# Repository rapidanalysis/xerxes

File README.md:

# Xerxes Pi — CM4/CM5 Carrier Board - Rev 2

## Overview
The **Xerxes Pi** is a compact, high-performance carrier board designed for the **Raspberry Pi Compute Module 4 (CM4)** and **Compute Module 5 (CM5)**. It integrates essential interfaces, intelligent power delivery, and expansion options suitable for both prototyping and embedded product deployment.

## Features

- **Dual Hirose 100-pin connectors** (0.5 mm pitch) compatible with CM4 and CM5  
- **USB-C port** for both **data and power**  
- **Gigabit Ethernet** interface with ESD protection
- **MicroSD card slot** for CM4 and CM5 Lite models  
- **M.2 M-Key connector** with onboard regulated power supply  
- **Boot-mode jumper** for eMMC variants of compute modules  
- **UART debug header** for serial console access  
- **I²C Qwiic connector** for peripheral expansion  
- **Fan header** for active cooling control  
- **External power input** connector  
- **Integrated PoE+ module** (IEEE 802.3at compliant)  
- **Indicator LEDs** for power and status monitoring

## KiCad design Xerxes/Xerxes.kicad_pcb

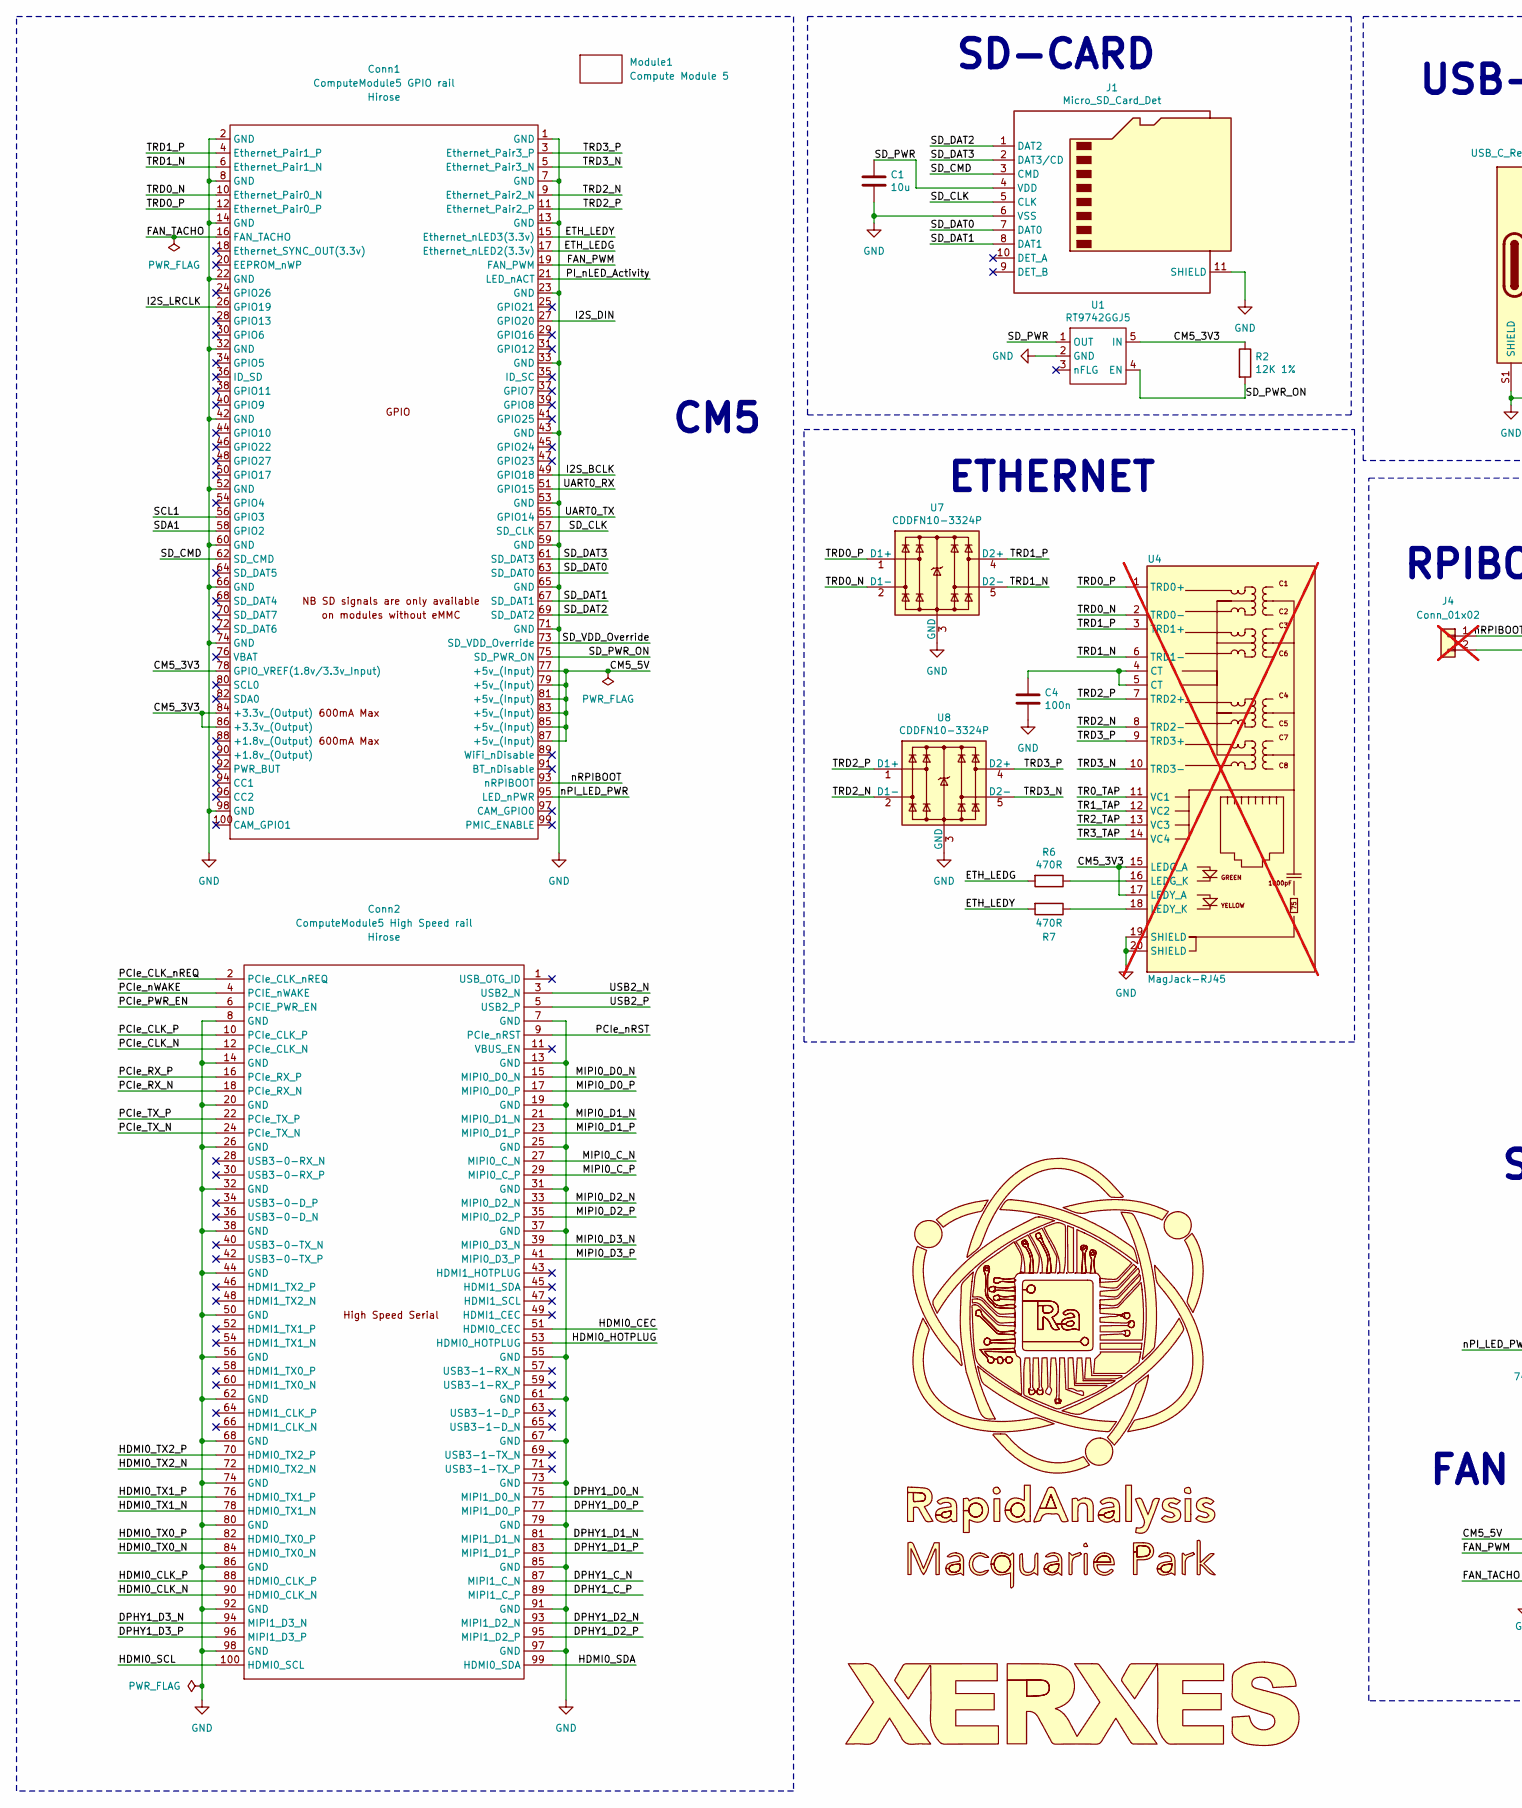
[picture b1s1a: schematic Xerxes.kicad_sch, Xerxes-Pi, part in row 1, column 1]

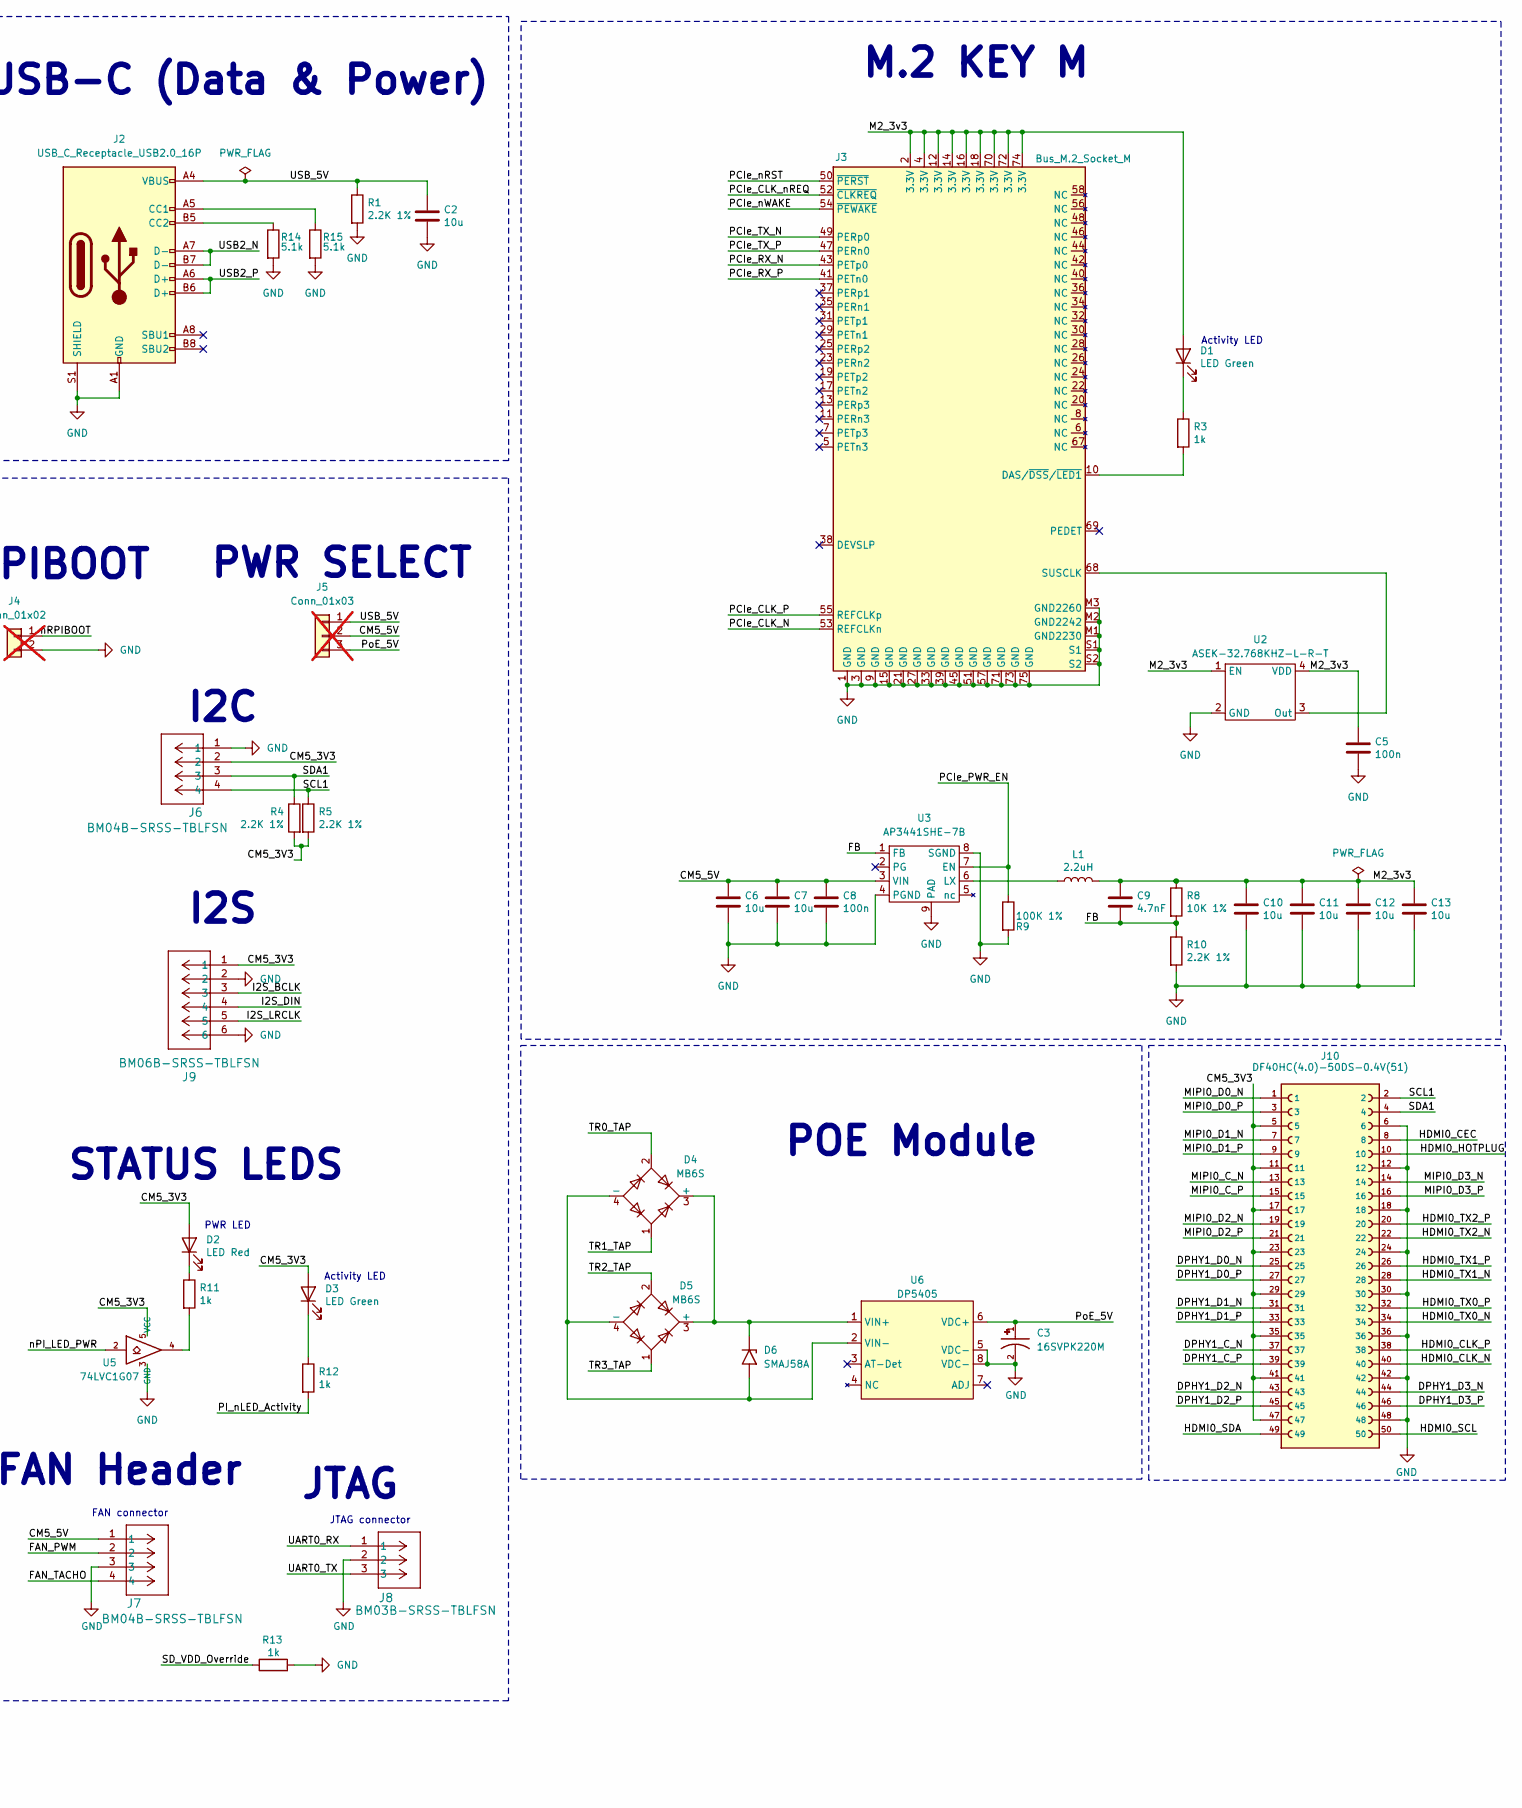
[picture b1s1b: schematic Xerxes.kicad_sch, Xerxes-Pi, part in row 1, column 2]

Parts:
C1, C2, C6, C7, C10, C11, C12, C13: 10u; C_0805_2012Metric; MPN GRM21BR71A106KA73L
C3: 16SVPK220M; CAP_16SVPK220M; MPN 16SVPK220M
C4, C5, C8: 100n; C_0402_1005Metric; MPN EMK105B7104KV-F
C9: 4.7nF; C_0402_1005Metric; MPN CC0402KRX7R9BB472
Conn1: ComputeModule5 GPIO rail; CONN_DF40C-100DS-0.4V51_HIR; MPN DF40C-100DS-0.4V(51)
Conn2: ComputeModule5 High Speed rail; CONN_DF40C-100DS-0.4V51_HIR; MPN DF40C-100DS-0.4V(51)
D1, D3: LED Green; LED_0603_1608Metric; MPN LTST-C190GKT
D2: LED Red; LED_0603_1608Metric; MPN LTST-C190KRKT
D4, D5: MB6S; TO-269AA; MPN MB6S
D6: SMAJ58A; D_SMA; MPN SMAJ58A
J1: Micro_SD_Card_Det; SDCARD_MOLEX_503398-1892; MPN 5033981892
J2: USB_C_Receptacle_USB2.0_16P; USB4205-GF-A; MPN USB4205-GF-A
J3: Bus_M.2_Socket_M; M.2 M Key socket; MPN MDT320M03001
J4: Conn_01x02; PinHeader_1x02_P2.54mm_Vertical; MPN G800W306018EU; not fitted
J5: Conn_01x03; PinHeader_1x03_P2.54mm_Vertical; MPN G800W305018EU; not fitted
J6, J7: BM04B-SRSS-TBLFSN; JST_SH_BM04B-SRSS-TB_1x04-1MP_P1.00mm_Vertical; MPN BM04B-SRSS-TBLFSN
J8: BM03B-SRSS-TBLFSN; JST_SH_BM03B-SRSS-TB_1x03-1MP_P1.00mm_Vertical; MPN BM03B-SRSS-TBLFSN
J9: BM06B-SRSS-TBLFSN; CONN_BM06B-SRSS-TB_JST; MPN BM06B-SRSS-TBLFSN
J10: DF40HC(4.0)-50DS-0.4V(51); HRS_DF40HC_4.0_-50DS-0.4V_51_; MPN DF40HC(4.0)-50DS-0.4V(51)
L1: 2.2uH; L_Bourns_SRP5030CC; MPN SRP5030CC-2R2M
Module1: Compute Module 5; Raspberry-Pi-5-Compute-Module
R1, R4, R5, R10: 2.2K 1%; R_0402_1005Metric; MPN RC0402FR-072K2L
R2: 12K 1%; R_0402_1005Metric; MPN RC0402FR-0712KL
R3, R11, R12, R13: 1k; R_0402_1005Metric; MPN RC0402FR-071KL
R6, R7: 470R; R_0402_1005Metric; MPN RC0402FR-07470RL
R8: 10K 1%; R_0402_1005Metric; MPN RC0402FR-0710KL
R9: 100K 1%; R_0402_1005Metric; MPN RC0402FR-07100KL
R14, R15: 5.1k; R_0603_1608Metric; MPN RC0603FR-075K1L
Sym1: Xerxes_Logo
Sym2: RapidAnalysis_Logo
U1: RT9742GGJ5; SOT-23-5; MPN RT9742GGJ5
U2: ASEK-32.768KHZ-L-R-T; Crystal_SMD_3225-4Pin_3.2x2.5mm; MPN ASEK-32.768KHZ-L-R-T
U3: AP3441SHE-7B; DFN-8-1EP_2x2mm_P0.5mm_EP1.05x1.75mm; MPN AP3441SHE-7B
U4: MagJack-RJ45; TRJG0926HENL; MPN LPJG0926HENL; not fitted
U5: 74LVC1G07; SOT-353_SC-70-5; MPN 74LVC1G07
U6: DP5405
U7, U8: CDDFN10-3324P; USON-10_2.5x1.0mm_P0.5mm; MPN CDDFN10-3324P

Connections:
/CM5_3V3: Conn1.78 (GPIO_VREF(1.8v/3.3v_Input)), Conn1.84 (+3.3v_(Output)), Conn1.86 (+3.3v_(Output)), D2.2 (A), D3.2 (A), J6.2, J9.1, J10.5, J10.11, J10.17, J10.23, J10.29, J10.35, J10.41, J10.47, R2.1, R4.2, R5.2, U1.5 (IN), U4.15 (LEDG_A), U4.17 (LEDY_A), U5.5 (VCC)
/CM5_5V: C6.1, C7.1, C8.1, Conn1.77 (+5v_(Input)), Conn1.79 (+5v_(Input)), Conn1.81 (+5v_(Input)), Conn1.83 (+5v_(Input)), Conn1.85 (+5v_(Input)), Conn1.87 (+5v_(Input)), J5.2, J7.1, U3.3 (VIN)
/DPHY1_C_N: Conn2.87 (MIPI1_C_N), J10.37
/DPHY1_C_P: Conn2.89 (MIPI1_C_P), J10.39
/DPHY1_D0_N: Conn2.75 (MIPI1_D0_N), J10.25
/DPHY1_D0_P: Conn2.77 (MIPI1_D0_P), J10.27
/DPHY1_D1_N: Conn2.81 (MIPI1_D1_N), J10.31
/DPHY1_D1_P: Conn2.83 (MIPI1_D1_P), J10.33
/DPHY1_D2_N: Conn2.93 (MIPI1_D2_N), J10.43
/DPHY1_D2_P: Conn2.95 (MIPI1_D2_P), J10.45
/DPHY1_D3_N: Conn2.94 (MIPI1_D3_N), J10.44
/DPHY1_D3_P: Conn2.96 (MIPI1_D3_P), J10.46
/ETH_LEDG: Conn1.17 (Ethernet_nLED2(3.3v)), R6.2
/ETH_LEDY: Conn1.15 (Ethernet_nLED3(3.3v)), R7.2
/FAN_PWM: Conn1.19 (FAN_PWM), J7.2
/FAN_TACHO: Conn1.16 (FAN_TACHO), J7.4
/FB: C9.2, R8.2, R10.1, U3.1 (FB)
/HDMI0_CEC: Conn2.51 (HDMI0_CEC), J10.8
/HDMI0_CLK_N: Conn2.90 (HDMI0_CLK_N), J10.40
/HDMI0_CLK_P: Conn2.88 (HDMI0_CLK_P), J10.38
/HDMI0_HOTPLUG: Conn2.53 (HDMI0_HOTPLUG), J10.10
/HDMI0_SCL: Conn2.100 (HDMI0_SCL), J10.50
/HDMI0_SDA: Conn2.99 (HDMI0_SDA), J10.49
/HDMI0_TX0_N: Conn2.84 (HDMI0_TX0_N), J10.34
/HDMI0_TX0_P: Conn2.82 (HDMI0_TX0_P), J10.32
/HDMI0_TX1_N: Conn2.78 (HDMI0_TX1_N), J10.28
/HDMI0_TX1_P: Conn2.76 (HDMI0_TX1_P), J10.26
/HDMI0_TX2_N: Conn2.72 (HDMI0_TX2_N), J10.22
/HDMI0_TX2_P: Conn2.70 (HDMI0_TX2_P), J10.20
/I2S_BCLK: Conn1.49 (GPIO18), J9.3
/I2S_DIN: Conn1.27 (GPIO20), J9.4
/I2S_LRCLK: Conn1.26 (GPIO19), J9.5
/M2_3v3: C5.1, C9.1, C10.1, C11.1, C12.1, C13.1, D1.2 (A), J3.2 (3.3V), J3.4 (3.3V), J3.12 (3.3V), J3.14 (3.3V), J3.16 (3.3V), J3.18 (3.3V), J3.70 (3.3V), J3.72 (3.3V), J3.74 (3.3V), L1.2, R8.1, U2.1 (EN), U2.4 (VDD)
/MIPI0_C_N: Conn2.27 (MIPI0_C_N), J10.13
/MIPI0_C_P: Conn2.29 (MIPI0_C_P), J10.15
/MIPI0_D0_N: Conn2.15 (MIPI0_D0_N), J10.1
/MIPI0_D0_P: Conn2.17 (MIPI0_D0_P), J10.3
/MIPI0_D1_N: Conn2.21 (MIPI0_D1_N), J10.7
/MIPI0_D1_P: Conn2.23 (MIPI0_D1_P), J10.9
/MIPI0_D2_N: Conn2.33 (MIPI0_D2_N), J10.19
/MIPI0_D2_P: Conn2.35 (MIPI0_D2_P), J10.21
/MIPI0_D3_N: Conn2.39 (MIPI0_D3_N), J10.14
/MIPI0_D3_P: Conn2.41 (MIPI0_D3_P), J10.16
/PCIe_CLK_N: Conn2.12 (PCIe_CLK_N), J3.53 (REFCLKn)
/PCIe_CLK_P: Conn2.10 (PCIe_CLK_P), J3.55 (REFCLKp)
/PCIe_CLK_nREQ: Conn2.2 (PCIe_CLK_nREQ), J3.52 (~CLKREQ)
/PCIe_PWR_EN: Conn2.6 (PCIE_PWR_EN), R9.1, U3.7 (EN)
/PCIe_RX_N: Conn2.18 (PCIe_RX_N), J3.43 (PETp0)
/PCIe_RX_P: Conn2.16 (PCIe_RX_P), J3.41 (PETn0)
/PCIe_TX_N: Conn2.24 (PCIe_TX_N), J3.49 (PERp0)
/PCIe_TX_P: Conn2.22 (PCIe_TX_P), J3.47 (PERn0)
/PCIe_nRST: Conn2.9 (PCIe_nRST), J3.50 (~PERST)
/PCIe_nWAKE: Conn2.4 (PCIE_nWAKE), J3.54 (~PEWAKE)
/PI_nLED_Activity: Conn1.21 (LED_nACT), R12.2
/PoE_5V: C3.1, J5.3, U6.6 (VDC+)
/SCL1: Conn1.56 (GPIO3), J6.4, J10.2, R5.1
/SDA1: Conn1.58 (GPIO2), J6.3, J10.4, R4.1
/SD_CLK: Conn1.57 (SD_CLK), J1.5 (CLK)
/SD_CMD: Conn1.62 (SD_CMD), J1.3 (CMD)
/SD_DAT0: Conn1.63 (SD_DAT0), J1.7 (DAT0)
/SD_DAT1: Conn1.67 (SD_DAT1), J1.8 (DAT1)
/SD_DAT2: Conn1.69 (SD_DAT2), J1.1 (DAT2)
/SD_DAT3: Conn1.61 (SD_DAT3), J1.2 (DAT3/CD)
/SD_PWR: C1.1, J1.4 (VDD), U1.1 (OUT)
/SD_PWR_ON: Conn1.75 (SD_PWR_ON), R2.2, U1.4 (EN)
/SD_VDD_Override: Conn1.73 (SD_VDD_Override), R13.1
/TR0_TAP: D4.2, U4.11 (VC1)
/TR1_TAP: D4.1, U4.12 (VC2)
/TR2_TAP: D5.2, U4.13 (VC3)
/TR3_TAP: D5.1, U4.14 (VC4)
/TRD0_N: Conn1.10 (Ethernet_Pair0_N), U4.2 (TRD0-), U7.2 (D1-), U7.9
/TRD0_P: Conn1.12 (Ethernet_Pair0_P), U4.1 (TRD0+), U7.1 (D1+), U7.10
/TRD1_N: Conn1.6 (Ethernet_Pair1_N), U4.6 (TRD1-), U7.5 (D2-), U7.6
/TRD1_P: Conn1.4 (Ethernet_Pair1_P), U4.3 (TRD1+), U7.4 (D2+), U7.7
/TRD2_N: Conn1.9 (Ethernet_Pair2_N), U4.8 (TRD2-), U8.2 (D1-), U8.9
/TRD2_P: Conn1.11 (Ethernet_Pair2_P), U4.7 (TRD2+), U8.1 (D1+), U8.10
/TRD3_N: Conn1.5 (Ethernet_Pair3_N), U4.10 (TRD3-), U8.5 (D2-), U8.6
/TRD3_P: Conn1.3 (Ethernet_Pair3_P), U4.9 (TRD3+), U8.4 (D2+), U8.7
/UART0_RX: Conn1.51 (GPIO15), J8.1
/UART0_TX: Conn1.55 (GPIO14), J8.3
/USB2_N: Conn2.3 (USB2_N), J2.A7 (D-), J2.B7 (D-)
/USB2_P: Conn2.5 (USB2_P), J2.A6 (D+), J2.B6 (D+)
/USB_5V: C2.1, J2.A4 (VBUS), J2.A9 (VBUS), J2.B4 (VBUS), J2.B9 (VBUS), J5.1, R1.1
/nPI_LED_PWR: Conn1.95 (LED_nPWR), U5.2
/nRPIBOOT: Conn1.93 (nRPIBOOT), J4.1
GND: C1.2, C2.2, C3.2, C4.2, C5.2, C6.2, C7.2, C8.2, C10.2, C11.2, C12.2, C13.2, Conn1.1 (GND), Conn1.2 (GND), Conn1.7 (GND), Conn1.8 (GND), Conn1.13 (GND), Conn1.14 (GND), Conn1.22 (GND), Conn1.23 (GND), Conn1.32 (GND), Conn1.33 (GND), Conn1.42 (GND), Conn1.43 (GND), Conn1.52 (GND), Conn1.53 (GND), Conn1.59 (GND), Conn1.60 (GND), Conn1.65 (GND), Conn1.66 (GND), Conn1.71 (GND), Conn1.74 (GND), Conn1.98 (GND), Conn2.7 (GND), Conn2.8 (GND), Conn2.13 (GND), Conn2.14 (GND), Conn2.19 (GND), Conn2.20 (GND), Conn2.25 (GND), Conn2.26 (GND), Conn2.31 (GND), Conn2.32 (GND), Conn2.37 (GND), Conn2.38 (GND), Conn2.44 (GND), Conn2.50 (GND), Conn2.55 (GND), Conn2.56 (GND), Conn2.61 (GND), Conn2.62 (GND), Conn2.67 (GND), Conn2.68 (GND), Conn2.73 (GND), Conn2.74 (GND), Conn2.79 (GND), Conn2.80 (GND), Conn2.85 (GND), Conn2.86 (GND), Conn2.91 (GND), Conn2.92 (GND), Conn2.97 (GND), Conn2.98 (GND), J1.6 (VSS), J1.11 (SHIELD), J2.A1 (GND), J2.A12 (GND), J2.B1 (GND), J2.B12 (GND), J2.S1 (SHIELD), J3.1 (GND), J3.3 (GND), J3.9 (GND), J3.15 (GND), J3.21 (GND), J3.27 (GND), J3.33 (GND), J3.39 (GND), J3.45 (GND), J3.51 (GND), J3.57 (GND), J3.71 (GND), J3.73 (GND), J3.75 (GND), J3.M1 (GND2230), J3.M2 (GND2242), J3.M3 (GND2260), J3.S1, J3.S2, J4.2, J6.1, J7.3, J8.2, J9.2, J9.6, J10.6, J10.12, J10.18, J10.24, J10.30, J10.36, J10.42, J10.48, R1.2, R9.2, R10.2, R13.2, R14.2, R15.2, U1.2 (GND), U2.2 (GND), U3.4 (PGND), U3.8 (SGND), U3.9 (PAD), U4.19 (SHIELD), U4.20 (SHIELD), U5.3 (GND), U6.5 (VDC-), U6.8 (VDC-), U7.3 (GND), U7.8 (GND), U8.3 (GND), U8.8 (GND)
unnamed: C4.1, U4.4 (CT), U4.5 (CT)
unnamed: D1.1 (K), R3.1
unnamed: D2.1 (K), R11.1
unnamed: D3.1 (K), R12.1
unnamed: D4.3 (+), D5.3 (+), D6.1 (A1), U6.1 (VIN+)
unnamed: D4.4 (-), D5.4 (-), D6.2 (A2), U6.2 (VIN-)
unnamed: J2.A5 (CC1), R15.1
unnamed: J2.B5 (CC2), R14.1
unnamed: J3.10 (DAS/~DSS/~LED1), R3.2
unnamed: J3.68 (SUSCLK), U2.3 (Out)
unnamed: R11.2, U5.4
unnamed: L1.1, U3.6 (LX)
unnamed: R6.1, U4.16 (LEDG_K)
unnamed: R7.1, U4.18 (LEDY_K)

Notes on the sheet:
USB-C (Data & Power)
JTAG connector
I2C
M.2 KEY M
POE Module
PWR SELECT
STATUS LEDS
Activity LED
PWR LED
I2S
FAN Header
FAN connector
RPIBOOT
JTAG
ETHERNET
CM5
SD-CARD

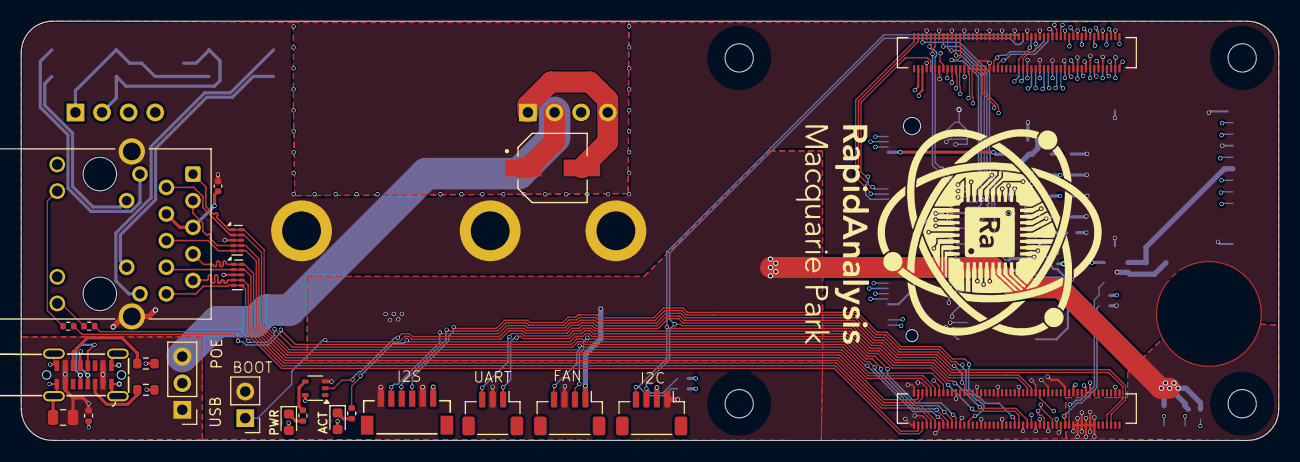
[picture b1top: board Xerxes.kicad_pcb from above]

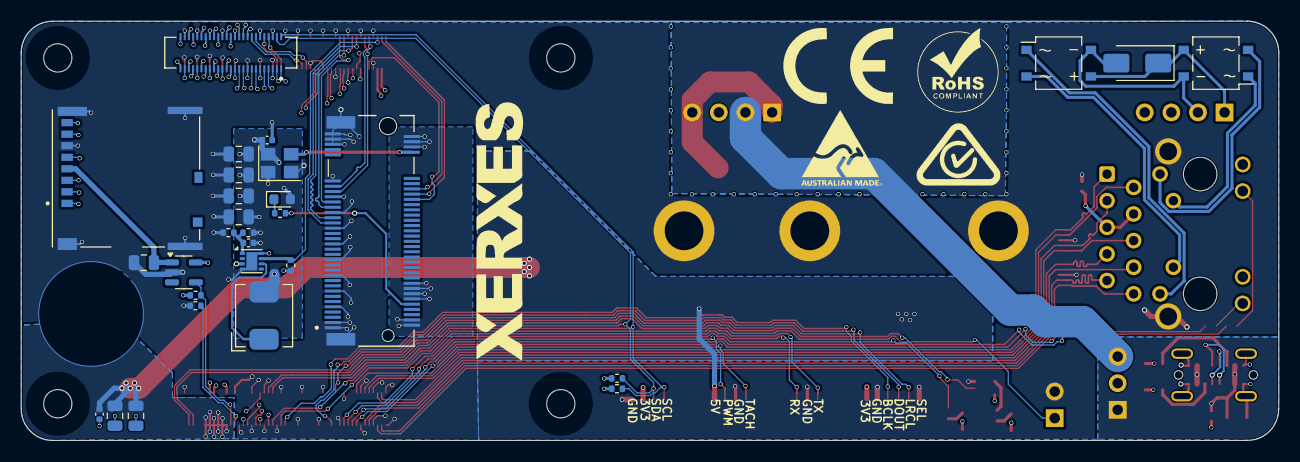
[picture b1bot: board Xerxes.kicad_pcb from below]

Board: 6 copper layers, 120.0 x 40.0 mm, 58 parts (30 on the bottom side), 100 nets.

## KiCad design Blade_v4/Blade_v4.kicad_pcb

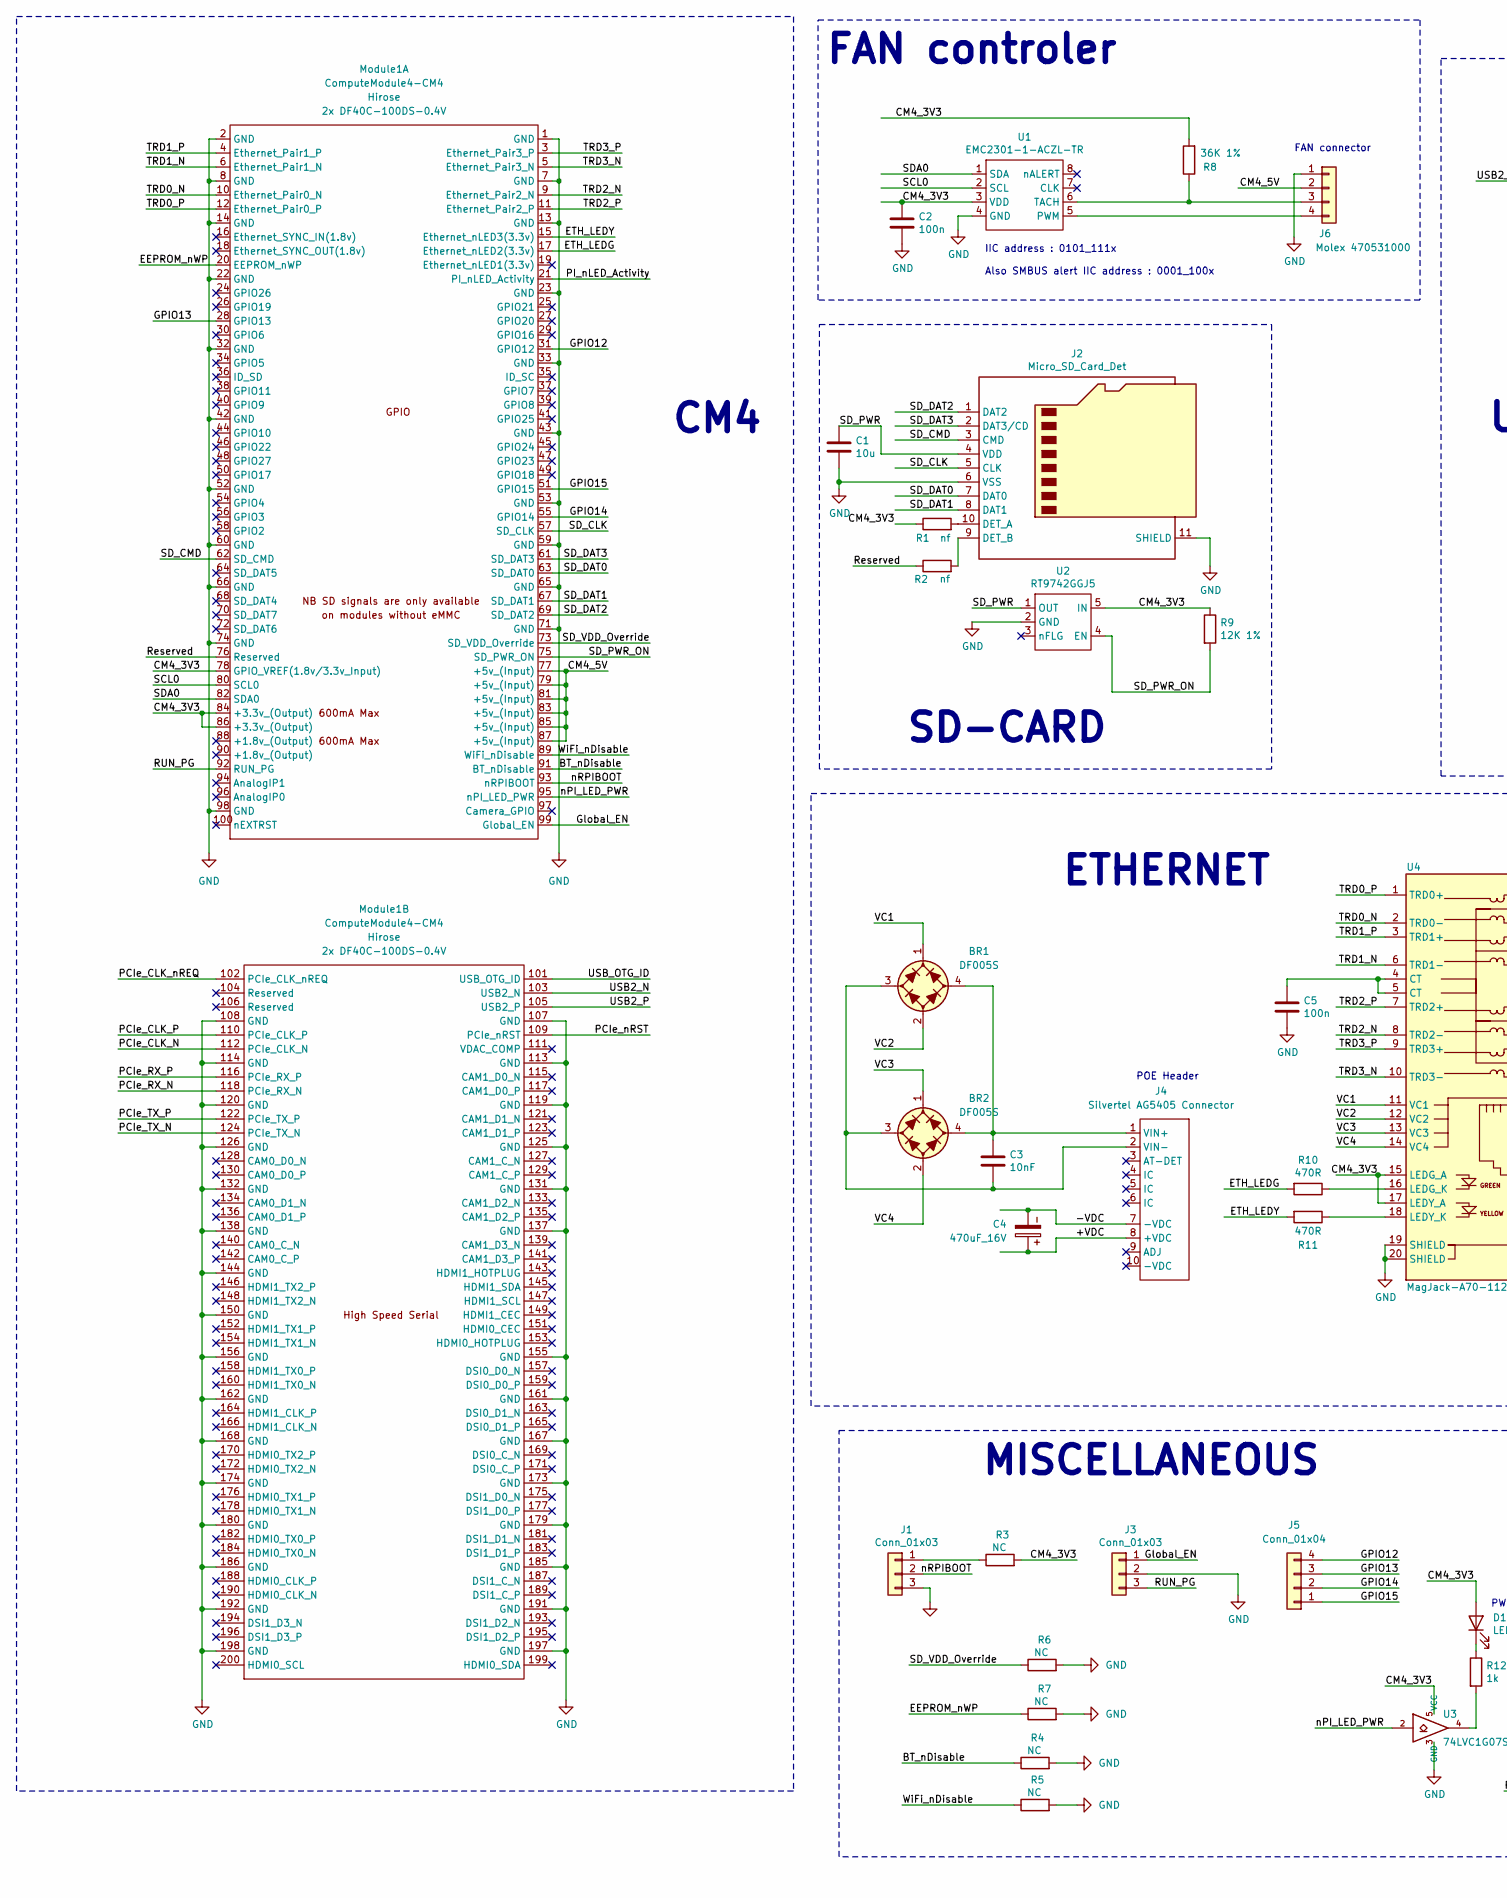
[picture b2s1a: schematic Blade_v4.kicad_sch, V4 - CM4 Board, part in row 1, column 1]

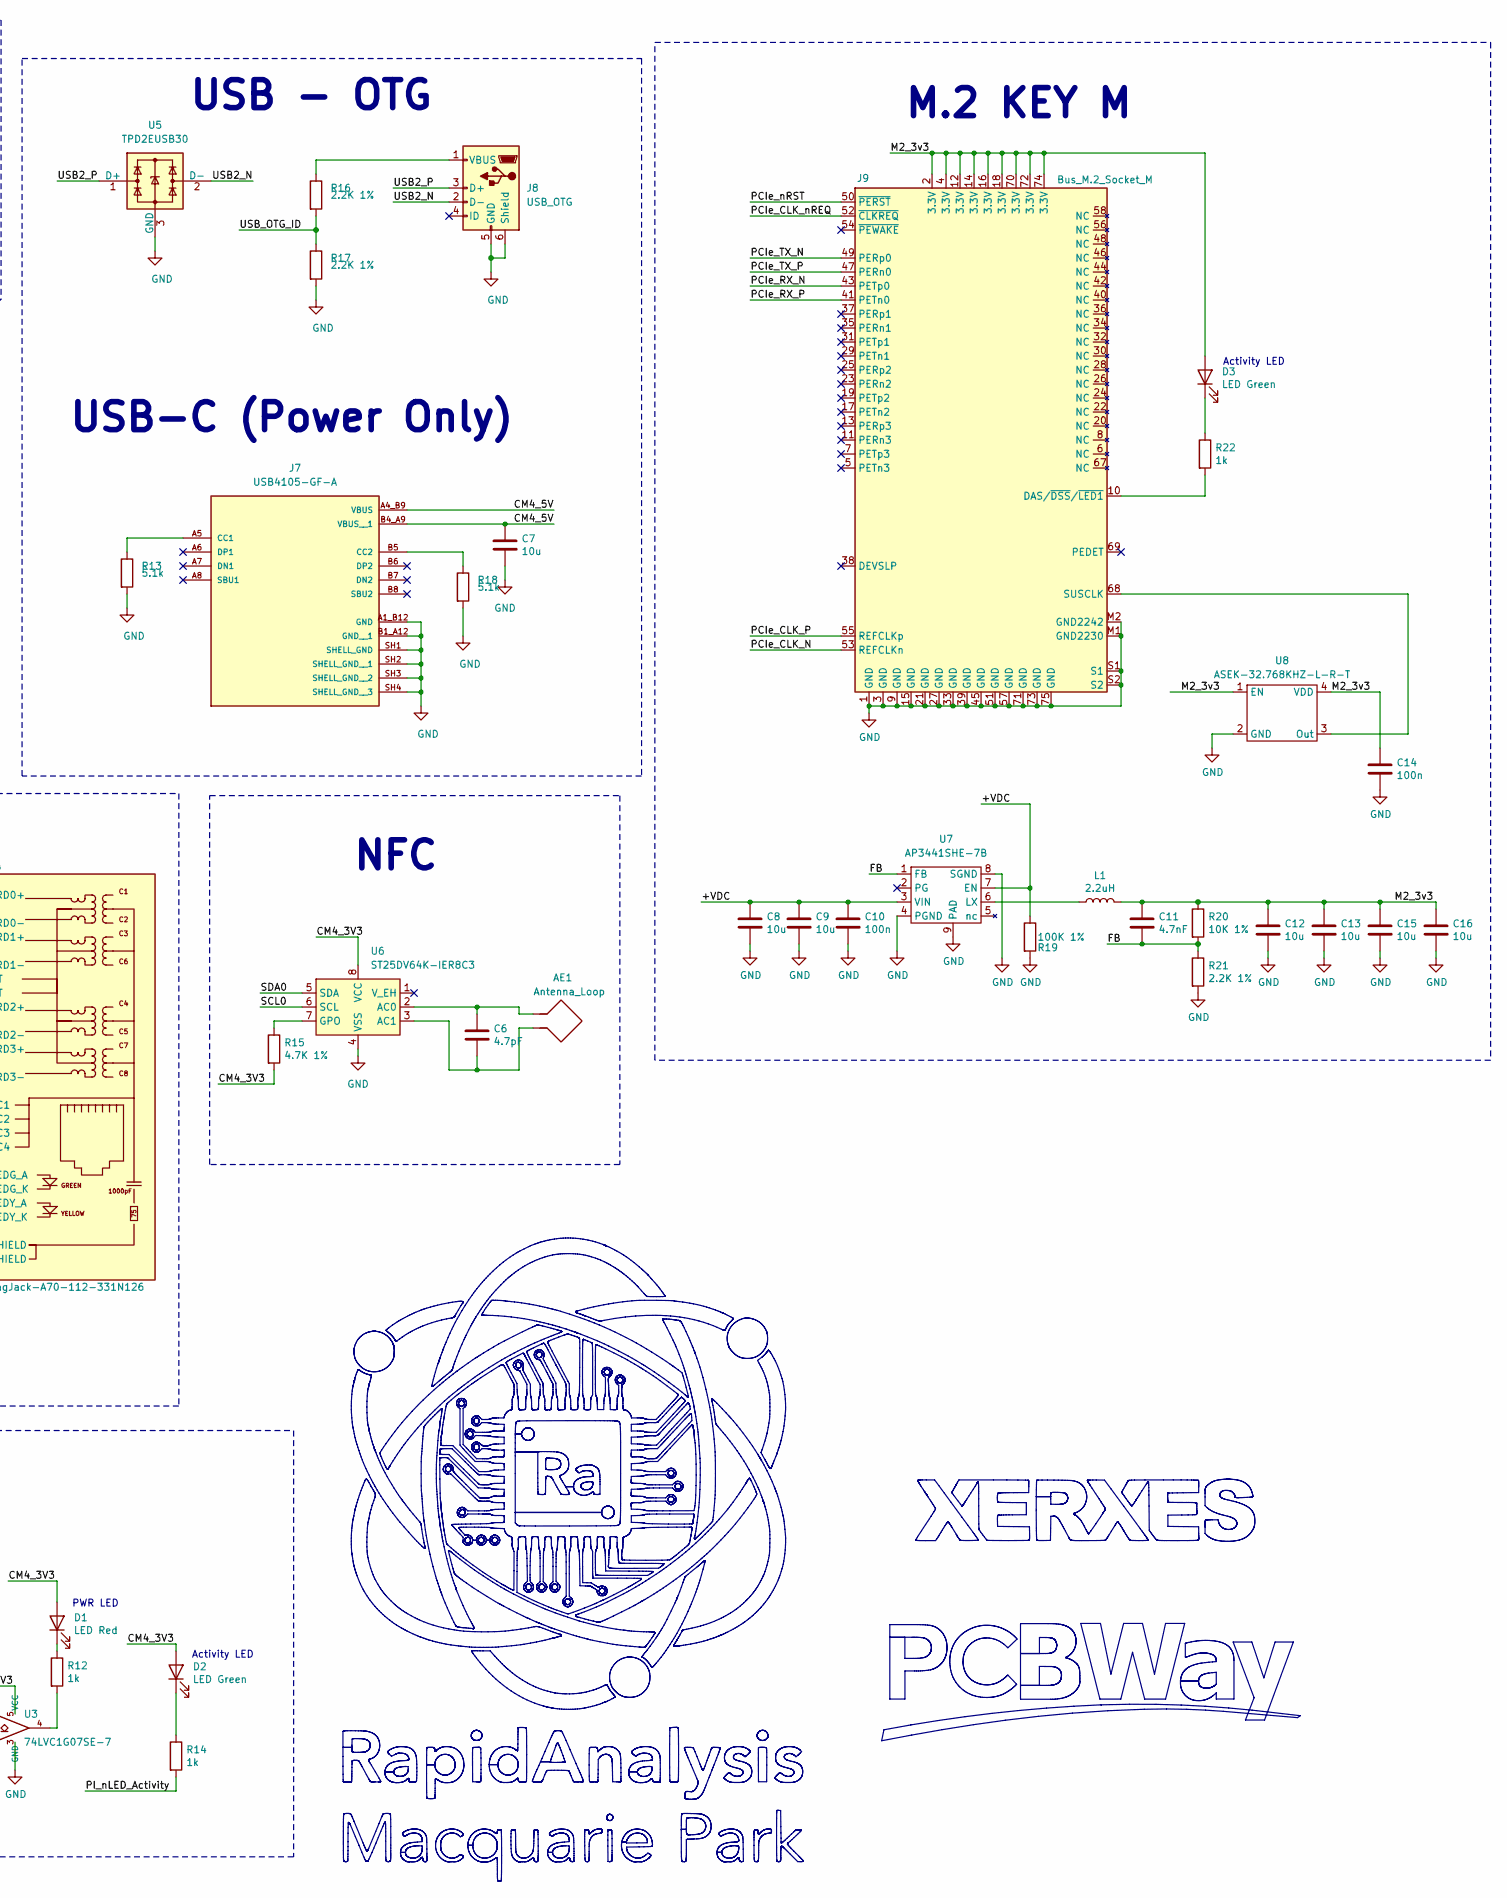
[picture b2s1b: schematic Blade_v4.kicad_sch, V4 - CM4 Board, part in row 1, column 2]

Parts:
AE1: Antenna_Loop; NFC_Antenna
BR1, BR2: DF005S; Diode_Bridge_Vishay_DFS
C1, C7, C8, C9, C12, C13, C15, C16: 10u; C_0805_2012Metric; Part Description 10uF 10% 10V Ceramic Capacitor X7R 0805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
C2, C5, C10, C14: 100n; C_0402_1005Metric; Part Description 0.1uF 10% 16V Ceramic Capacitor X7R 040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
C3: 10nF; C_0402_1005Metric; Part Description 10nF capacitor 0402
C4: 470uF_16V; CP_Radial_D8.0mm_P3.50mm
C6: 4.7pF; C_0402_1005Metric; Part Description 4.7pF capacitor 0402
C11: 4.7nF; C_0402_1005Metric; Part Description 4.7nF capacitor 0402
D1: LED Red; LED_0603_1608Metric; Part Description Red 620nm LED Indication - Discrete 2.2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
D2, D3: LED Green; LED_0603_1608Metric; Part Description Green 572nm LED Indication - Discrete 2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
J1, J3: Conn_01x03; PinHeader_1x03_P2.54mm_Vertical; Part Description 3pin 0.1" connector
J2: Micro_SD_Card_Det; SDCARD_MOLEX_503398-1892; Part Description 9 (8 + 1) Position Card Connector micro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
J4: Silvertel AG5405 Connector; Converter_DCDC_Silvertel_Ag54xx
J5: Conn_01x04; PinHeader_1x04_P2.54mm_Vertical
J6: Molex 470531000; FanPinHeader_1x04_P2.54mm_Vertical; Part Description Connector Header Through Hole 4 positio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
J7: USB4105-GF-A; GCT_USB4105-GF-A; PARTREV B4
J8: USB_OTG; USB_Micro-B_EDAC_UCON00686; MPN 10103594-0001LF; Digi-Key_PN 609-4050-1-ND
J9: Bus_M.2_Socket_M; M.2 M Key socket; Part Description M.2 M Key connector
L1: 2.2uH; L_Bourns_SRP5030CC; Part Description Inductor, SMT, 2520, 2u2, IRMS=7A, ISAT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
Module1: ComputeModule4-CM4; Raspberry-Pi-4-Compute-Module
R1, R2: nf; R_0402_1005Metric; Part Description Resistor 1K M1005 1% 63mW
R3, R4, R5, R6, R7: NC; R_0402_1005Metric; Part Description Resistor 1K M1005 1% 63mW
R8: 36K 1%; R_0402_1005Metric; Part Description Resistor 36K M1005 1% 63mW
R9: 12K 1%; R_0402_1005Metric; Part Description Resistor 12K M1005 1% 63mW
R10, R11: 470R; R_0402_1005Metric; Part Description Resistor 470R M1005 1% 63mW
R12, R14, R22: 1k; R_0402_1005Metric; Part Description Resistor 1K M1005 1% 63mW
R13, R18: 5.1k; R_0603_1608Metric_Pad0.98x0.95mm_HandSolder; MPN RC0603FR-075K1L; Digi-Key_PN 311-5.10KHRCT-ND
R15: 4.7K 1%; R_0402_1005Metric; Part Description Resistor 4.7K M1005 1% 63mW
R16, R17: 2.2K 1%; R_0603_1608Metric_Pad0.98x0.95mm_HandSolder; MPN RC0603FR-072K2L; Digi-Key_PN 311-2.20KHRCT-ND
R19: 100K 1%; R_0402_1005Metric; Part Description Resistor 100K M1005 1% 63mW
R20: 10K 1%; R_0402_1005Metric; Part Description Resistor 10K M1005 1% 63mW
R21: 2.2K 1%; R_0402_1005Metric; Part Description Resistor 2.2K M1005 1% 63mW
U1: EMC2301-1-ACZL-TR; MSOP-8_3x3mm_P0.65mm; Part Description Motor Driver PWM 8-MSOP
U2: RT9742GGJ5; SOT-23-5; Part Description Power Switch/Driver 1:1 N-Channel 1A TS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
U3: 74LVC1G07SE-7; SOT-353_SC-70-5; Part Description Buffer, Non-Inverting 1 Element 1 Bit p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
U4: MagJack-A70-112-331N126; TRJG0926HENL; Part Description Gigabit Ethernet Magjack
U5: TPD2EUSB30; Texas_DRT-3; MPN TPD2EUSB30DRTR; Digi-Key_PN 296-25509-1-ND
U6: ST25DV64K-IER8C3; DFN-8-1EP_3x2mm_P0.5mm_EP1.36x1.46mm
U7: AP3441SHE-7B; DFN-8-1EP_2x2mm_P0.5mm_EP1.05x1.75mm; Part Description 3A DC-DC converter
U8: ASEK-32.768KHZ-L-R-T; Crystal_SMD_3225-4Pin_3.2x2.5mm; Part Description 32KHz Xtal oscilator

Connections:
/+VDC: C4.1, C8.1, C9.1, C10.1, J4.8 (+VDC), R19.1, U7.3 (VIN), U7.7 (EN)
/-VDC: C4.2, J4.7 (-VDC)
/BT_nDisable: Module1.91 (BT_nDisable), R4.1
/CM4_3V3: C2.1, D1.2 (A), D2.2 (A), Module1.78 (GPIO_VREF(1.8v/3.3v_Input)), Module1.84 (+3.3v_(Output)), Module1.86 (+3.3v_(Output)), R1.1, R3.2, R8.2, R9.1, R15.2, U1.3 (VDD), U2.5 (IN), U3.5 (VCC), U4.15 (LEDG_A), U4.17 (LEDY_A), U6.8 (VCC)
/CM4_5V: C7.1, J6.2, J7.A4_B9 (VBUS), J7.B4_A9 (VBUS__1), Module1.77 (+5v_(Input)), Module1.79 (+5v_(Input)), Module1.81 (+5v_(Input)), Module1.83 (+5v_(Input)), Module1.85 (+5v_(Input)), Module1.87 (+5v_(Input))
/EEPROM_nWP: Module1.20 (EEPROM_nWP), R7.1
/ETH_LEDG: Module1.17 (Ethernet_nLED2(3.3v)), R10.2
/ETH_LEDY: Module1.15 (Ethernet_nLED3(3.3v)), R11.2
/FB: C11.2, R20.2, R21.1, U7.1 (FB)
/GPIO12: J5.4, Module1.31 (GPIO12)
/GPIO13: J5.3, Module1.28 (GPIO13)
/GPIO14: J5.2, Module1.55 (GPIO14)
/GPIO15: J5.1, Module1.51 (GPIO15)
/Global_EN: J3.1, Module1.99 (Global_EN)
/M2_3v3: C11.1, C12.1, C13.1, C14.1, C15.1, C16.1, D3.2 (A), J9.2 (3.3V), J9.4 (3.3V), J9.12 (3.3V), J9.14 (3.3V), J9.16 (3.3V), J9.18 (3.3V), J9.70 (3.3V), J9.72 (3.3V), J9.74 (3.3V), L1.2, R20.1, U8.1 (EN), U8.4 (VDD)
/PCIe_CLK_N: J9.53 (REFCLKn), Module1.112 (PCIe_CLK_N)
/PCIe_CLK_P: J9.55 (REFCLKp), Module1.110 (PCIe_CLK_P)
/PCIe_CLK_nREQ: J9.52 (~CLKREQ), Module1.102 (PCIe_CLK_nREQ)
/PCIe_RX_N: J9.43 (PETp0), Module1.118 (PCIe_RX_N)
/PCIe_RX_P: J9.41 (PETn0), Module1.116 (PCIe_RX_P)
/PCIe_TX_N: J9.49 (PERp0), Module1.124 (PCIe_TX_N)
/PCIe_TX_P: J9.47 (PERn0), Module1.122 (PCIe_TX_P)
/PCIe_nRST: J9.50 (~PERST), Module1.109 (PCIe_nRST)
/PI_nLED_Activity: Module1.21 (PI_nLED_Activity), R14.2
/RUN_PG: J3.3, Module1.92 (RUN_PG)
/Reserved: Module1.76 (Reserved), R2.1
/SCL0: Module1.80 (SCL0), U1.2 (SCL), U6.6 (SCL)
/SDA0: Module1.82 (SDA0), U1.1 (SDA), U6.5 (SDA)
/SD_CLK: J2.5 (CLK), Module1.57 (SD_CLK)
/SD_CMD: J2.3 (CMD), Module1.62 (SD_CMD)
/SD_DAT0: J2.7 (DAT0), Module1.63 (SD_DAT0)
/SD_DAT1: J2.8 (DAT1), Module1.67 (SD_DAT1)
/SD_DAT2: J2.1 (DAT2), Module1.69 (SD_DAT2)
/SD_DAT3: J2.2 (DAT3/CD), Module1.61 (SD_DAT3)
/SD_PWR: C1.1, J2.4 (VDD), U2.1 (OUT)
/SD_PWR_ON: Module1.75 (SD_PWR_ON), R9.2, U2.4 (EN)
/SD_VDD_Override: Module1.73 (SD_VDD_Override), R6.1
/TRD0_N: Module1.10 (Ethernet_Pair0_N), U4.2 (TRD0-)
/TRD0_P: Module1.12 (Ethernet_Pair0_P), U4.1 (TRD0+)
/TRD1_N: Module1.6 (Ethernet_Pair1_N), U4.6 (TRD1-)
/TRD1_P: Module1.4 (Ethernet_Pair1_P), U4.3 (TRD1+)
/TRD2_N: Module1.9 (Ethernet_Pair2_N), U4.8 (TRD2-)
/TRD2_P: Module1.11 (Ethernet_Pair2_P), U4.7 (TRD2+)
/TRD3_N: Module1.5 (Ethernet_Pair3_N), U4.10 (TRD3-)
/TRD3_P: Module1.3 (Ethernet_Pair3_P), U4.9 (TRD3+)
/USB2_N: J8.2 (D-), Module1.103 (USB2_N), U5.2 (D-)
/USB2_P: J8.3 (D+), Module1.105 (USB2_P), U5.1 (D+)
/USB_OTG_ID: Module1.101 (USB_OTG_ID), R16.2, R17.1
/VC1: BR1.1 (+), U4.11 (VC1)
/VC2: BR1.2 (-), U4.12 (VC2)
/VC3: BR2.1 (+), U4.13 (VC3)
/VC4: BR2.2 (-), U4.14 (VC4)
/WiFi_nDisable: Module1.89 (WiFi_nDisable), R5.1
/nPI_LED_PWR: Module1.95 (nPI_LED_PWR), U3.2
/nRPIBOOT: J1.2, Module1.93 (nRPIBOOT)
GND: C1.2, C2.2, C5.2, C7.2, C8.2, C9.2, C10.2, C12.2, C13.2, C14.2, C15.2, C16.2, J1.3, J2.6 (VSS), J2.11 (SHIELD), J3.2, J6.1, J7.A1_B12 (GND), J7.B1_A12 (GND__1), J7.SH1 (SHELL_GND), J7.SH2 (SHELL_GND__1), J7.SH3 (SHELL_GND__2), J7.SH4 (SHELL_GND__3), J8.5 (GND), J8.6 (Shield), J9.1 (GND), J9.3 (GND), J9.9 (GND), J9.15 (GND), J9.21 (GND), J9.27 (GND), J9.33 (GND), J9.39 (GND), J9.45 (GND), J9.51 (GND), J9.57 (GND), J9.71 (GND), J9.73 (GND), J9.75 (GND), J9.M1 (GND2230), J9.M2 (GND2242), J9.S1, J9.S2, Module1.1 (GND), Module1.2 (GND), Module1.7 (GND), Module1.8 (GND), Module1.13 (GND), Module1.14 (GND), Module1.22 (GND), Module1.23 (GND), Module1.32 (GND), Module1.33 (GND), Module1.42 (GND), Module1.43 (GND), Module1.52 (GND), Module1.53 (GND), Module1.59 (GND), Module1.60 (GND), Module1.65 (GND), Module1.66 (GND), Module1.71 (GND), Module1.74 (GND), Module1.98 (GND), Module1.107 (GND), Module1.108 (GND), Module1.113 (GND), Module1.114 (GND), Module1.119 (GND), Module1.120 (GND), Module1.125 (GND), Module1.126 (GND), Module1.131 (GND), Module1.132 (GND), Module1.137 (GND), Module1.138 (GND), Module1.144 (GND), Module1.150 (GND), Module1.155 (GND), Module1.156 (GND), Module1.161 (GND), Module1.162 (GND), Module1.167 (GND), Module1.168 (GND), Module1.173 (GND), Module1.174 (GND), Module1.179 (GND), Module1.180 (GND), Module1.185 (GND), Module1.186 (GND), Module1.191 (GND), Module1.192 (GND), Module1.197 (GND), Module1.198 (GND), R4.2, R5.2, R6.2, R7.2, R13.2, R17.2, R18.2, R19.2, R21.2, U1.4 (GND), U2.2 (GND), U3.3 (GND), U4.19 (SHIELD), U4.20 (SHIELD), U5.3 (GND), U6.4 (VSS), U7.4 (PGND), U7.8 (SGND), U7.9 (PAD), U8.2 (GND)
unnamed: BR1.3 (1), BR2.3 (1), C3.2, J4.2 (VIN-)
unnamed: BR1.4 (2), BR2.4 (2), C3.1, J4.1 (VIN+)
unnamed: C5.1, U4.4 (CT), U4.5 (CT)
unnamed: D1.1 (K), R12.1
unnamed: D2.1 (K), R14.1
unnamed: D3.1 (K), R22.1
unnamed: J1.1, R3.1
unnamed: J2.10 (DET_A), R1.2
unnamed: J2.9 (DET_B), R2.2
unnamed: J6.3, R8.1, U1.6 (TACH)
unnamed: J6.4, U1.5 (PWM)
unnamed: J7.A5 (CC1), R13.1
unnamed: J7.B5 (CC2), R18.1
unnamed: J8.1 (VBUS), R16.1
unnamed: J9.10 (DAS/~DSS/~LED1), R22.2
unnamed: J9.68 (SUSCLK), U8.3 (Out)
unnamed: R12.2, U3.4
unnamed: R10.1, U4.16 (LEDG_K)
unnamed: R11.1, U4.18 (LEDY_K)
unnamed: AE1.1, C6.1, U6.2 (AC0)
unnamed: AE1.2, C6.2, U6.3 (AC1)
unnamed: R15.1, U6.7 (GPO)
unnamed: L1.1, U7.6 (LX)

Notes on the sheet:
USB-C (Power Only)
FAN controler
M.2 KEY M
NFC
Activity LED
IIC address : 0101_111x
FAN connector
PWR LED
USB - OTG
POE Header
Also SMBUS alert IIC address : 0001_100x
MISCELLANEOUS
ETHERNET
CM4
SD-CARD

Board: 2 copper layers, 63 parts (4 on the bottom side), 79 nets, no tracks yet.

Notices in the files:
rpi-cm4-usb-uSD/rpi-cm4-usb-uSD/rpi-cm4-usb-uSD.kicad_pcb:
creativecommons.org/licenses/by/4.0
License: CC BY-SA 4.0
parts and their libraries:
Copyright 2016 Accelerated Designs. All rights reserved.
